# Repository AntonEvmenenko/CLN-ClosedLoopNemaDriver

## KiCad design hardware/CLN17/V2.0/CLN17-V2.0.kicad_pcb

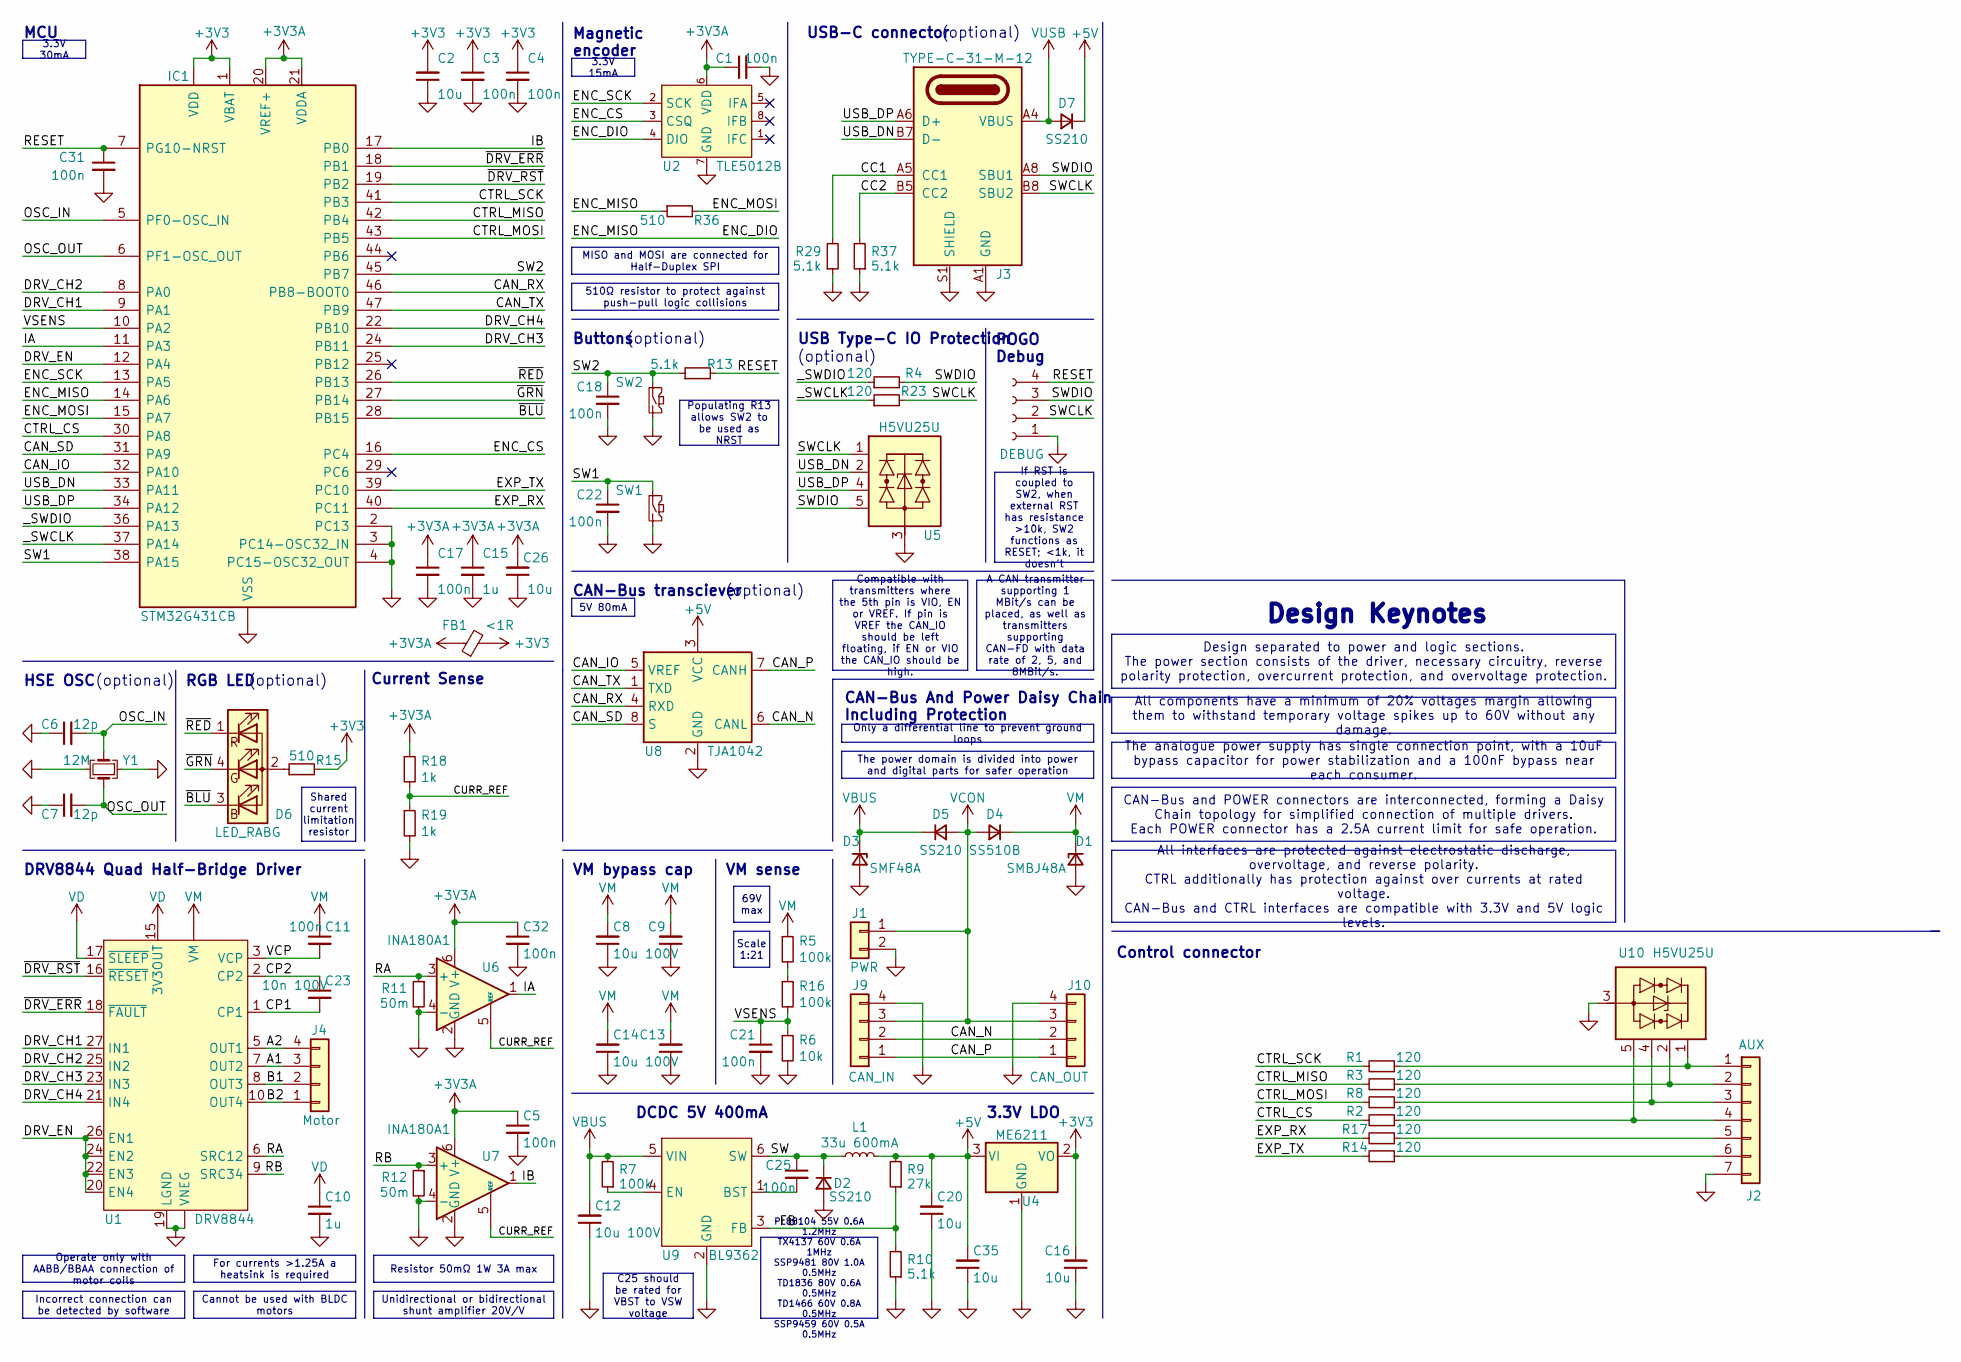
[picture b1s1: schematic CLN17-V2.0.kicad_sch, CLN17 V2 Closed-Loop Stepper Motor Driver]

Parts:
C1, C3, C4, C5, C11, C17, C18, C21, C22, C25, C31, C32: 100n; C0402; Part Type Basic; LCSC Part # C1525
C2, C16, C20, C26, C35: 10u; C0402; Part Type Basic; LCSC Part # C15525
C6, C7: 12p; C0402; Part Type Basic; LCSC Part # C1547
C8, C9, C12, C13, C14: 10u 100V; C1210; Part Type Extended; LCSC Part # C5156756
C10, C15: 1u; C0402; Part Type Basic; LCSC Part # C52923
C23: 10n 100V; C0402; Part Type Extended; LCSC Part # C527014
D1: SMBJ48A; D_SMB; Part Type Extended; LCSC Part # C353356
D2, D5, D7: SS210; D_SOD-123F; Part Type Extended; LCSC Part # C183475
D3: SMF48A; D_SOD-123F; Part Type Extended; LCSC Part # C353279
D4: SS510B; D_SMB; Part Type Extended; LCSC Part # C7420368
D6: LED_RABG; LED_RGB_0606; Part Type Extended; LCSC Part # C2874115
FB1: <1R; R0402; LCSC Part # C76883
IC1: STM32G431CB; QFN-48-1EP_7x7mm_P0.5mm_EP5.6x5.6mm; Part Type Extended; LCSC Part # C529356
J1: PWR; XH2.54 2P; Part Type Extended; LCSC Part # C2908611
J2: AUX; JST-S7B-ZR
J3: TYPE-C-31-M-12; USB-TYPE-C-31-M-12; Part Type Extended; LCSC Part # C2988369
J4: Motor; XH2.54 4P; Part Type Extended; LCSC Part # C5188444
J8: DEBUG; SWD; Part Type -----
J9: CAN_IN; PH2.0 4P; Part Type Extended; LCSC Part # C5188444
J10: CAN_OUT; PH2.0 4P; Part Type Extended; LCSC Part # C5188444
L1: 33u 600mA; CD32; Part Type Extended; LCSC Part # C492262
R1, R2, R3, R4, R8, R14, R17, R23: 120; R0402; Part Type Basic; LCSC Part # C25079
R5, R7, R16: 100k; R0402; Part Type Basic; LCSC Part # C25741
R6: 10k; R0402; Part Type Basic; LCSC Part # C25744
R9: 27k; R0402; Part Type Basic; LCSC Part # C25771
R10, R13, R29, R37: 5.1k; R0402; Part Type Basic; LCSC Part # C25941
R11, R12: 50m; R1206_Shunt; Part Type Extended; LCSC Part # C2924516
R15, R36: 510; R0402; Part Type Basic; LCSC Part # C25123
R18, R19: 1k; R0402; Part Type Basic; LCSC Part # C25741
SW1, SW2: SW_Push; SW_SPST_PTS810; Part Type Extended; LCSC Part # C2888430
U1: DRV8844; HTSSOP-28-1EP_4.4x9.7mm_P0.65mm_EP2.85x5.4mm; Part Type Extended; LCSC Part # C177807
U2: TLE5012B; SOIC-8_3.9x4.9mm_P1.27mm; Part Type Extended; LCSC Part # C123083
U4: ME6211; SOT-23-3; Part Type Basic; LCSC Part # C168807
U5, U10: H5VU25U; DFN-2510; Part Type Basic; LCSC Part # C7420374
U6, U7: INA180A1; SOT-23-6; Part Type Extended; LCSC Part # C122228
U8: TJA1042; HVSON-8-1EP_3x3mm_P0.65mm_EP1.6x2.4mm; Part Type Extended; LCSC Part # C131480
U9: BL9362; SOT-23-6; Part Type Extended; LCSC Part # C2909086
Y1: 12M; Crystal-3225-4P; Part Type Basic; LCSC Part # C9002

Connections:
+3V3: C2.2, C3.1, C4.1, C16.2, FB1.2, IC1.1 (VBAT), IC1.23 (VDD), IC1.35 (VDD), IC1.48 (VDD), R15.2, U4.2 (VO)
+3V3A: C1.1, C5.1, C15.1, C17.1, C26.2, C32.1, FB1.1, IC1.20 (VREF+), IC1.21 (VDDA), R18.1, U2.6 (VDD), U6.6 (V+), U7.6 (V+)
+5V: C20.2, C35.2, D7.1 (K), L1.2, R9.2, U4.3 (VI), U8.3 (VCC)
/A1: J4.3, U1.7 (OUT2)
/A2: J4.4, U1.5 (OUT1)
/B1: J4.2, U1.8 (OUT3)
/B2: J4.1, U1.10 (OUT4)
/CAN_IO: IC1.32 (PA10), U8.5 (VREF)
/CAN_N: J9.2, J10.2, U8.6 (CANL)
/CAN_P: J9.1, J10.1, U8.7 (CANH)
/CAN_RX: IC1.46 (PB8-BOOT0), U8.4 (RXD)
/CAN_SD: IC1.31 (PA9), U8.8 (S)
/CAN_TX: IC1.47 (PB9), U8.1 (TXD)
/CC1: J3.A5 (CC1), R29.2
/CC2: J3.B5 (CC2), R37.2
/CP1: C23.2, U1.1 (CP1)
/CP2: C23.1, U1.2 (CP2)
/CTRL_CS: IC1.30 (PA8), R2.2
/CTRL_MISO: IC1.42 (PB4), R3.2
/CTRL_MOSI: IC1.43 (PB5), R8.2
/CTRL_SCK: IC1.41 (PB3), R1.2
/CURR_REF: R18.2, R19.1, U6.5 (REF), U7.5 (REF)
/DRV_CH1: IC1.9 (PA1), U1.27 (IN1)
/DRV_CH2: IC1.8 (PA0), U1.25 (IN2)
/DRV_CH3: IC1.24 (PB11), U1.23 (IN3)
/DRV_CH4: IC1.22 (PB10), U1.21 (IN4)
/DRV_EN: IC1.12 (PA4), U1.20 (EN4), U1.22 (EN3), U1.24 (EN2), U1.26 (EN1)
/ENC_CS: IC1.16 (PC4), U2.3 (CSQ)
/ENC_DIO: IC1.14 (PA6), R36.1, U2.4 (DIO)
/ENC_MOSI: IC1.15 (PA7), R36.2
/ENC_SCK: IC1.13 (PA5), U2.2 (SCK)
/EXP_RX: IC1.40 (PC11), R17.2
/EXP_TX: IC1.39 (PC10), R14.2
/FB: R9.1, R10.2, U9.3 (FB)
/IA: IC1.11 (PA3), U6.1
/IB: IC1.17 (PB0), U7.1
/OSC_IN: C6.2, IC1.5 (PF0-OSC_IN), Y1.1
/OSC_OUT: C7.2, IC1.6 (PF1-OSC_OUT), Y1.3
/RA: R11.1, U1.6 (SRC12), U6.3 (+)
/RB: R12.1, U1.9 (SRC34), U7.3 (+)
/RESET: C31.1, IC1.7 (PG10-NRST), J8.4, R13.2
/SW: C25.1, D2.1 (K), L1.1, U9.6 (SW)
/SW1: C22.1, IC1.38 (PA15), SW1.1
/SW2: C18.1, IC1.45 (PB7), R13.1, SW2.1
/SWCLK: J3.B8 (SBU2), J8.2, R23.2, U5.1 (I/O1), U5.10
/SWDIO: J3.A8 (SBU1), J8.3, R4.2, U5.5 (I/O4), U5.6 (I/O4)
/USB_DN: IC1.33 (PA11), J3.A7 (D-), J3.B7 (D-), U5.2 (I/O2), U5.9 (I/O2)
/USB_DP: IC1.34 (PA12), J3.A6 (D+), J3.B6 (D+), U5.4 (I/O3), U5.7 (I/O3)
/VCP: C11.2, U1.3 (VCP)
/VSENS: C21.1, IC1.10 (PA2), R6.1, R16.2
/_SWCLK: IC1.37 (PA14), R23.1
/_SWDIO: IC1.36 (PA13), R4.1
/~BLU: D6.3 (BK), IC1.28 (PB15)
/~CTRL_5V: IC1.25 (PB12)
/~DRV_ERR: IC1.18 (PB1), U1.18 (~FAULT)
/~DRV_RST: IC1.19 (PB2), U1.16 (~RESET)
/~GRN: D6.4 (GK), IC1.27 (PB14)
/~RED: D6.1 (RK), IC1.26 (PB13)
GND: C1.2, C2.1, C3.2, C4.2, C5.2, C6.1, C7.1, C8.1, C9.1, C10.2, C12.1, C13.1, C14.1, C15.2, C16.1, C17.2, C18.2, C20.1, C21.2, C22.2, C26.1, C31.2, C32.2, C35.1, D1.2 (A), D2.2 (A), D3.2 (A), IC1.2 (PC13), IC1.3 (PC14-OSC32_IN), IC1.4 (PC15-OSC32_OUT), IC1.49 (VSS), J1.2, J2.7, J3.A1 (GND), J3.A12 (GND), J3.B1 (GND), J3.B12 (GND), J3.S1 (SHIELD), J8.1, J9.4, J10.4, R6.2, R10.1, R11.2, R12.2, R19.2, R29.1, R37.1, SW1.2, SW2.2, U1.14 (VNEG), U1.19 (LGND), U1.28 (VNEG), U1.29 (VNEG), U2.7 (GND), U4.1 (GND), U5.3 (GND), U5.8 (GND), U6.2 (GND), U6.4 (-), U7.2 (GND), U7.4 (-), U8.2 (GND), U8.9 (GND), U9.2 (GND), U10.3 (GND), U10.8 (GND), Y1.2, Y1.4
unnamed: D6.2 (A), R15.1
unnamed: J2.1, R1.1, U10.1 (I/O1), U10.10
unnamed: J2.2, R3.1, U10.2 (I/O2), U10.9 (I/O2)
unnamed: J2.3, R8.1, U10.4 (I/O3), U10.7 (I/O3)
unnamed: J2.4, R2.1, U10.5 (I/O4), U10.6 (I/O4)
unnamed: J2.5, R17.1
unnamed: J2.6, R14.1
unnamed: R5.2, R16.1
unnamed: C25.2, U9.1 (BST)
unnamed: R7.1, U9.4 (EN)
VBUS: C12.2, D3.1 (K), D5.1 (K), R7.2, U9.5 (VIN)
VCON: D4.2 (A), D5.2 (A), J1.1, J9.3, J10.3
VD: C10.1, U1.15 (3V3OUT), U1.17 (~SLEEP)
VM: C8.2, C9.2, C11.1, C13.2, C14.2, D1.1 (K), D4.1 (K), R5.1, U1.4 (VM), U1.11 (VM)
VUSB: D7.2 (A), J3.A4 (VBUS), J3.A9 (VBUS), J3.B4 (VBUS), J3.B9 (VBUS)

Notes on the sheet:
Operate only with AABB/BBAA connection of motor coils
Cannot be used with BLDC motors
CAN-Bus and POWER connectors are interconnected, forming a Daisy Chain topology for simplified connection of multiple drivers. Each POWER connector has a 2.5A current limit for safe operation.
Only a differential line to prevent ground loops
3.3V 30mA
A CAN transmitter supporting 1 MBit/s can be placed, as well as transmitters supporting CAN-FD with data rate of 2, 5, and 8MBit/s.
If RST is coupled to SW2, when external RST has resistance >10k, SW2 functions as RESET; <1k, it doesn't
The power domain is divided into power and digital parts for safer operation
Design separated to power and logic sections. The power section consists of the driver, necessary circuitry, reverse polarity protection, overcurrent protection, and overvoltage protection.
Shared current limitation resistor
C25 should be rated for VBST to VSW voltage
Unidirectional or bidirectional shunt amplifier 20V/V
Scale 1:21
Compatible with transmitters where the 5th pin is VIO, EN or VREF. If pin is VREF the CAN_IO should be left floating, if EN or VIO the CAN_IO should be high.
3.3V 15mA
Incorrect connection can be detected by software
PL88104 55V 0.6A 1.2MHz TX4137 60V 0.6A 1MHz SSP9481 80V 1.0A 0.5MHz TD1836 80V 0.6A 0.5MHz TD1466 60V 0.8A 0.5MHz SSP9459 60V 0.5A 0.5MHz
5V 80mA
Populating R13 allows SW2 to be used as NRST
All components have a minimum of 20% voltages margin allowing them to withstand temporary voltage spikes up to 60V without any damage.
Resistor 50mΩ 1W 3A max
69V max
All interfaces are protected against electrostatic discharge, overvoltage, and reverse polarity. CTRL additionally has protection against over currents at rated voltage. CAN-Bus and CTRL interfaces are compatible with 3.3V and 5V logic levels.
510Ω resistor to protect against push-pull logic collisions
The analogue power supply has single connection point, with a 10uF bypass capacitor for power stabilization and a 100nF bypass near each consumer.
For currents >1.25A a heatsink is required
MISO and MOSI are connected for Half-Duplex SPI
CAN-Bus And Power Daisy Chain Including Protection
(optional)
Magnetic encoder
MCU
CAN-Bus transciever
Control connector
DCDC 5V 400mA
VM bypass cap
USB-C connector
Current Sense
POGO Debug
DRV8844 Quad Half-Bridge Driver
Design Keynotes

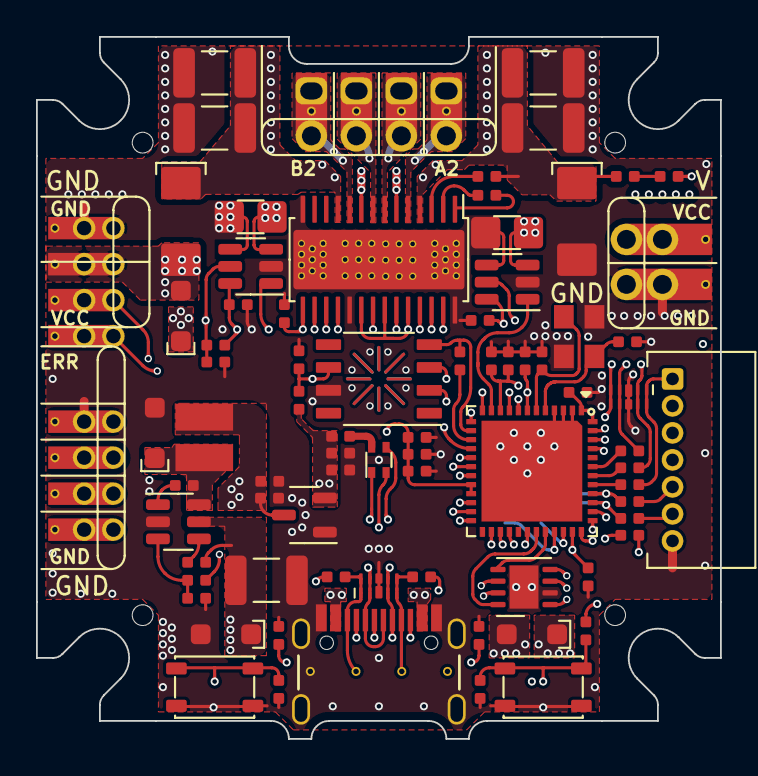
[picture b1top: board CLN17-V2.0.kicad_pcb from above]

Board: 4 copper layers, 38.0 x 39.0 mm, 79 parts (1 on the bottom side), 73 nets.

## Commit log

2025-07-31 [WIP] Before adding CAN connectors
2025-07-31 Added .gitignore
2025-08-02 [WIP] Before rotating the CAN transceiver
2025-08-09 Almost done
2025-08-09 Minor PCB refactoring

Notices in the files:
hardware/CLN17/V2.0/CLN17-V2.0.kicad_sch:
https://creativecommons.org/licenses/by-nc-sa/4.0
